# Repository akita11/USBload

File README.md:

# USBload
Dummy USB load

## これは何？
マイコンボードやLEDなどをモバイルバッテリーで駆動させるとき、急に電源が切れてしまうことはありませんか？
大抵のモバイルバッテリーは消費電流が弱い時にスリープするようになっています。

本モジュールをモバイルバッテリーに取り付けることで、定期的に負荷電流を流すことで、モバイルバッテリーをスリープさせないようにすることができます。

本モジュールは間欠で電流を流すことで、モバイルバッテリーの動作時間により影響を与えないようにしました。
また、端子を結線することで、消費電流値と電流の間欠期間を設定できます。
それにより、使用するモバイルバッテリーの挙動に合わせ、動作を調整することができます。

## USBloadとUSBload2の違い
モバイルバッテリーによってオス側が差し込めないものがあるとのご意見を戴き、USBload2はAタイプのオスコネクタをつけました。

※USBload2.1では使用するマイコンがSTC8G1K08に変更になっていますが、使い方は変更ありません。

## 使い方
モバイルバッテリーに本モジュールのオス側を差し込み、メスコネクタに給電用USBケーブルを差し込むだけです。

※使用するモバイルバッテリーにあわせて、以下の「設定」を行う必要があります。

## 設定

### 電流間欠期間の設定方法

本モジュールを接続しない状態で、モバイルバッテリーをONにし、その後、自動的にスリープに入る（給電が止まる）までの時間を計測します。その時間に応じて、以下のとおり間欠期間を設定します。

間欠期間は、上記画像の赤色のA,Bパターンをショートすることで設定できます。

|A|B|間欠期間|補足|
|----|----|----|----|
|オープン|オープン|約24秒|30秒でスリープするモバイルバッテリー向け|
|ショート|オープン|約16秒|20秒でスリープするモバイルバッテリー向け|
|オープン|ショート|約12秒|15秒でスリープするモバイルバッテリー向け|
|ショート|ショート|約8秒|10秒でスリープするモバイルバッテリー向け|

### 消費電流値の設定方法
デフォルトで100mA流れるようになっており、上記画像の青色のパターンを1つショートするごとに電流値が100mA増えます。
多くのモバイルバッテリーは100mAのままでスリープを回避できるようですが、より多くの電流が必要なものもありますので、100mAのままではスリープを回避できない場合は、順に流す電流を増やしてください、

## その他
サイズ(USBload) : 18×12×10.5mm
サイズ(USBload2) : 35.6×17×11mm
モジュールの消費電流値 : 100mA～400mA  
モジュールの電流増減インターバル : 約10～30秒  

## （参考：自作する方向け）

USBload2.1（使用マイコン: STC8G1K08）のプログラムの書き込み方法はUSBload21_pgm.pdfを参照してください。

## 終わりに

USBloadの改良点がありましたら、ぜひIsuuesに書いてください。
こんな作品に作ったよ！という方は [#USBload](https://twitter.com/search?q=%23USBload&src=typed_query) を付けてSNSなどで公開してくださると嬉しいです。

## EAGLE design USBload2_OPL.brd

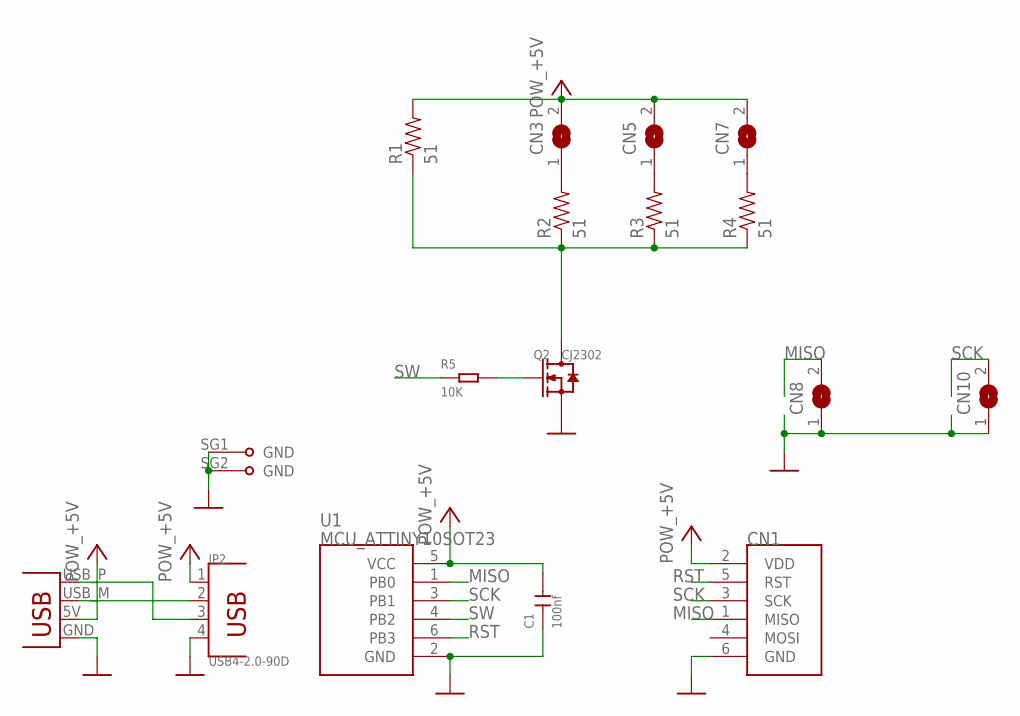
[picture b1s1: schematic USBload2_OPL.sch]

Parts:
C1: 100nf; C0603
CN1: CON_AVRISPTH; 2X03R
CN3, CN5, CN7, CN8, CN10: JUMPER_SJ
JP1: CON_USBPCB; USB-A-PCB
JP2: USB4-2.0-90D; USB4+2P-2.0-90D
Q2: CJ2302; SOT-23
R1, R2, R3, R4: 51; 0805
R5: 10K; R0603
U1: MCU_ATTINY10SOT23; SOT23-6

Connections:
+5V: C1.2, CN1.2 (VDD), CN3.2, CN5.2, CN7.2, JP1.5V (VBUS), JP2.1, R1.2, U1.5 (VCC)
GND: C1.1, CN1.6 (GND), CN8.1, CN10.1, JP1.GND, JP2.4, JP2.SG1 (GND), JP2.SG2 (GND), Q2.2 (S), U1.2 (GND)
MISO: CN1.1 (MISO), CN8.2, U1.1 (PB0)
unnamed: JP1.USB_M (D-), JP2.2
unnamed: JP1.USB_P (D+), JP2.3
unnamed: CN5.1, R3.2
unnamed: CN3.1, R2.2
unnamed: CN7.1, R4.2
unnamed: Q2.1 (G), R5.2
unnamed: Q2.3 (D), R1.1, R2.1, R3.1, R4.1
RST: CN1.5 (RST), U1.6 (PB3)
SCK: CN1.3 (SCK), CN10.2, U1.3 (PB1)
SW: R5.1, U1.4 (PB2)

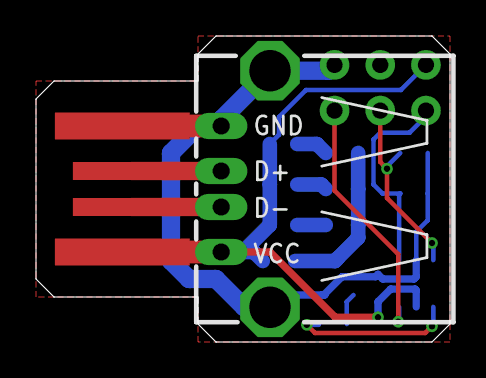
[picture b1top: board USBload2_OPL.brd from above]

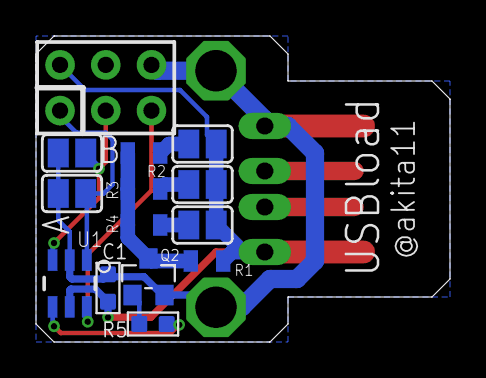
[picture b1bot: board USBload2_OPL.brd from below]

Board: 2 copper layers, 23.0 x 17.0 mm, 16 parts (14 on the bottom side), 13 nets.

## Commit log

2018-10-03 add PCB data
2018-10-03 add Arduino source
2018-10-09 Readmeの説明を追加
2018-10-09 設定方法を追記
2018-10-09 readmeを推敲
2020-07-08 USBload2に関する説明を追加
2021-05-15 ファイル名の整理とUSBload2のデータの追加
